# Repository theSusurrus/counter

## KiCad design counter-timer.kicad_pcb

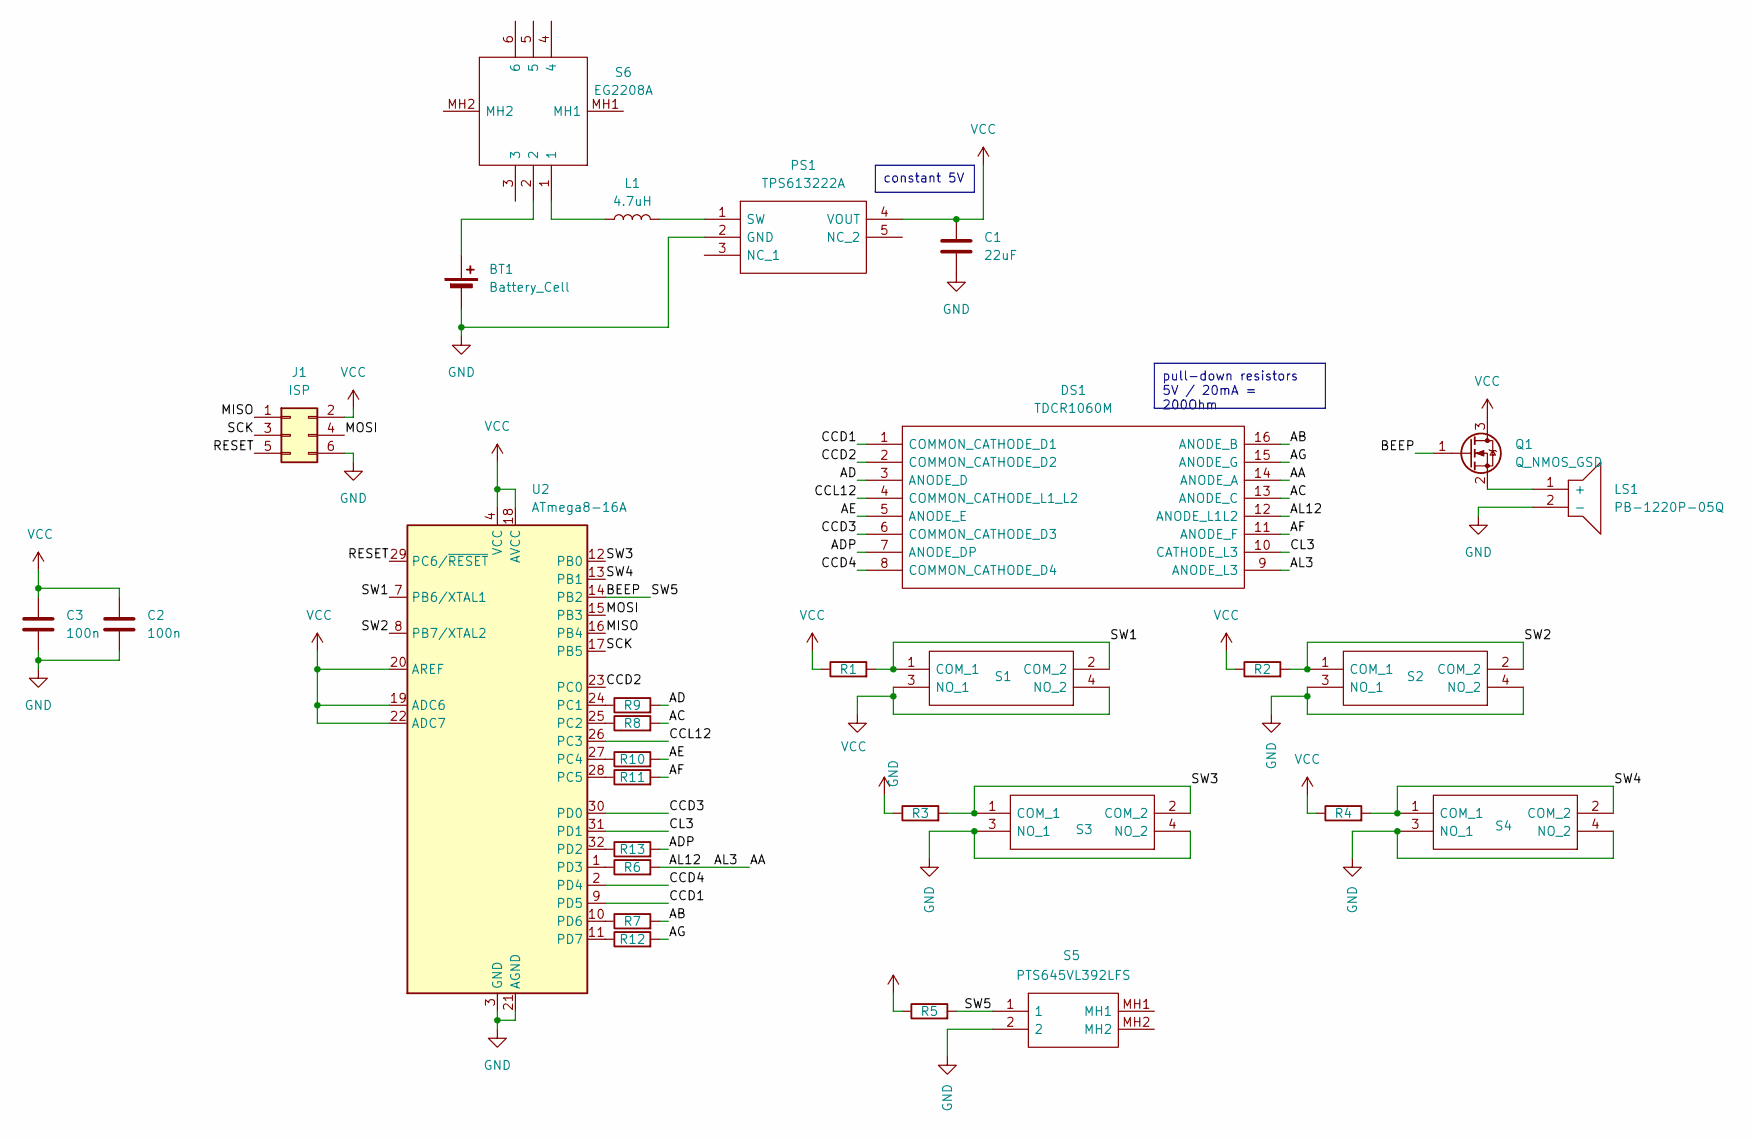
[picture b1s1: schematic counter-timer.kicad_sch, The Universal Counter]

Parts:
BT1: Battery_Cell; 12BH311PRGR
C1: 22uF; C_0603_1608Metric_Pad1.08x0.95mm_HandSolder
C2, C3: 100n; C_0603_1608Metric_Pad1.08x0.95mm_HandSolder
DS1: TDCR1060M; DIPS1016W50P254L4020H725Q16N; Mouser Part Number 78-TDCR1060M
J1: ISP; PinHeader_2x03_P2.54mm_Vertical
L1: 4.7uH; L_2512_6332Metric_Pad1.52x3.35mm_HandSolder
LS1: PB-1220P-05Q; PB1220P05Q; Mouser Part Number 539-PB-1220P-05Q
PS1: TPS613222A; SOT95P280X145-5N; Mouser Part Number 595-TPS613221ADBVR
Q1: Q_NMOS_GSD; TSOT-23_HandSoldering
R1, R2, R3, R4, R5: 1k; R_0603_1608Metric_Pad0.98x0.95mm_HandSolder
R6, R7, R8, R9, R10, R11, R12, R13: 200; R_0603_1608Metric_Pad0.98x0.95mm_HandSolder
S1, S2, S3, S4: FSM6JH; Mouser Part Number 506-FSM6JH
S5: PTS645VL392LFS; Mouser Part Number 611-PTS645VL392
S6: EG2208A; Mouser Part Number 612-EG2208A
U2: ATmega8-16A; TQFP-32_7x7mm_P0.8mm

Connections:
/AA: DS1.9 (ANODE_L3), DS1.12 (ANODE_L1L2), DS1.14 (ANODE_A), R6.2
/AB: DS1.16 (ANODE_B), R7.2
/AC: DS1.13 (ANODE_C), R8.2
/AD: DS1.3 (ANODE_D), R9.2
/ADP: DS1.7 (ANODE_DP), R13.2
/AE: DS1.5 (ANODE_E), R10.2
/AF: DS1.11 (ANODE_F), R11.2
/AG: DS1.15 (ANODE_G), R12.2
/BEEP: Q1.1 (G), R5.2, S5.1, U2.14 (PB2)
/CCD1: DS1.1 (COMMON_CATHODE_D1), U2.9 (PD5)
/CCD2: DS1.2 (COMMON_CATHODE_D2), U2.23 (PC0)
/CCD3: DS1.6 (COMMON_CATHODE_D3), U2.30 (PD0)
/CCD4: DS1.8 (COMMON_CATHODE_D4), U2.2 (PD4)
/CCL12: DS1.4 (COMMON_CATHODE_L1_L2), U2.26 (PC3)
/CL3: DS1.10 (CATHODE_L3), U2.31 (PD1)
/MISO: J1.1, U2.16 (PB4)
/MOSI: J1.4, U2.15 (PB3)
/RESET: J1.5, U2.29 (PC6/~RESET)
/SCK: J1.3, U2.17 (PB5)
/SW1: R1.2, S1.1 (COM_1), S1.2 (COM_2), U2.7 (PB6/XTAL1)
/SW2: R2.2, S2.1 (COM_1), S2.2 (COM_2), U2.8 (PB7/XTAL2)
/SW3: R3.2, S3.1 (COM_1), S3.2 (COM_2), U2.12 (PB0)
/SW4: R4.2, S4.1 (COM_1), S4.2 (COM_2), U2.13 (PB1)
GND: BT1.2 (-), C1.2, C2.2, C3.2, J1.6, LS1.2 (-), PS1.2 (GND), S1.3 (NO_1), S1.4 (NO_2), S2.3 (NO_1), S2.4 (NO_2), S3.3 (NO_1), S3.4 (NO_2), S4.3 (NO_1), S4.4 (NO_2), S5.2, U2.3 (GND), U2.5 (GND), U2.21 (AGND)
unnamed: BT1.1 (+), S6.2
unnamed: L1.1, S6.1
unnamed: LS1.1 (+), Q1.2 (S)
unnamed: L1.2, PS1.1 (SW)
unnamed: R9.1, U2.24 (PC1)
unnamed: R8.1, U2.25 (PC2)
unnamed: R10.1, U2.27 (PC4)
unnamed: R11.1, U2.28 (PC5)
unnamed: R13.1, U2.32 (PD2)
unnamed: R6.1, U2.1 (PD3)
unnamed: R7.1, U2.10 (PD6)
unnamed: R12.1, U2.11 (PD7)
VCC: C1.1, C2.1, C3.1, J1.2, PS1.4 (VOUT), Q1.3 (D), R1.1, R2.1, R3.1, R4.1, R5.1, U2.4 (VCC), U2.6 (VCC), U2.18 (AVCC), U2.19 (ADC6), U2.20 (AREF), U2.22 (ADC7)

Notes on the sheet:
constant 5V
pull-down resistors 5V / 20mA = 200Ohm

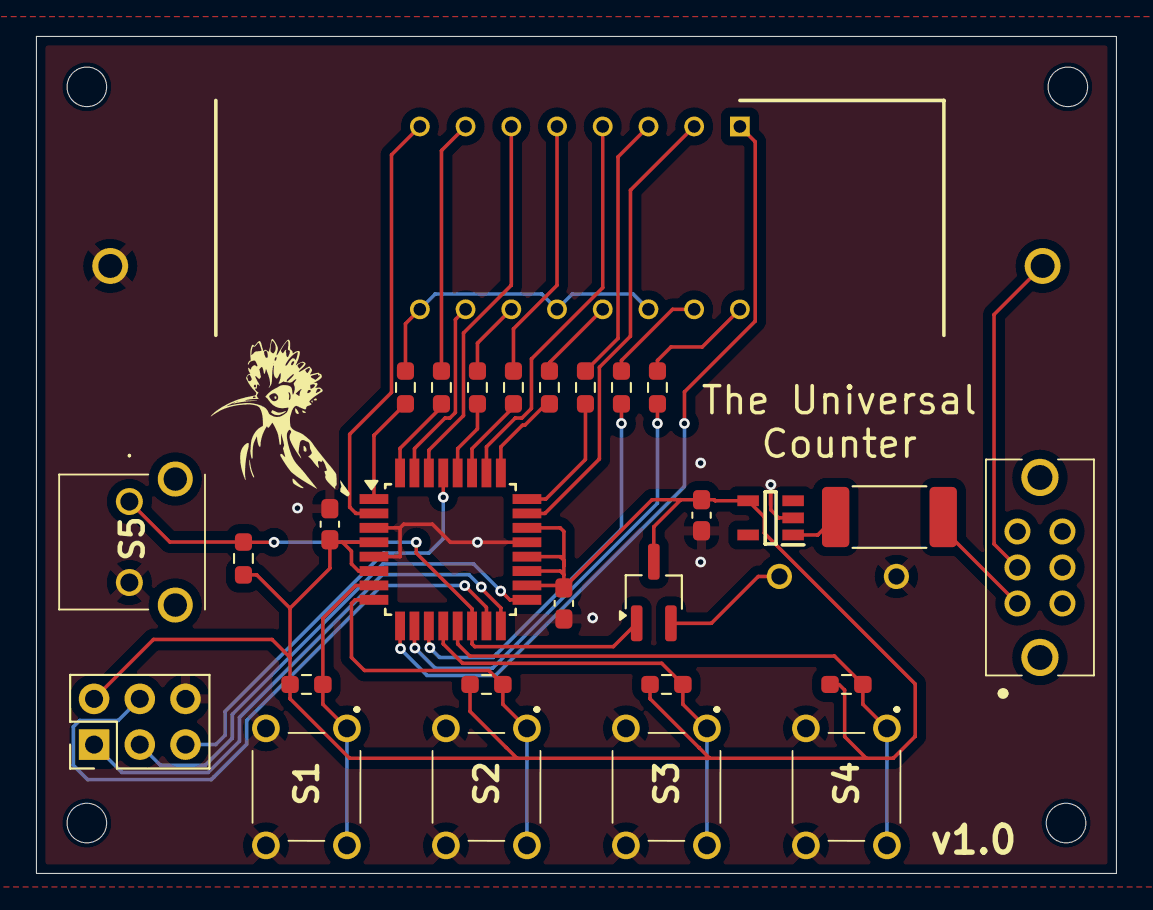
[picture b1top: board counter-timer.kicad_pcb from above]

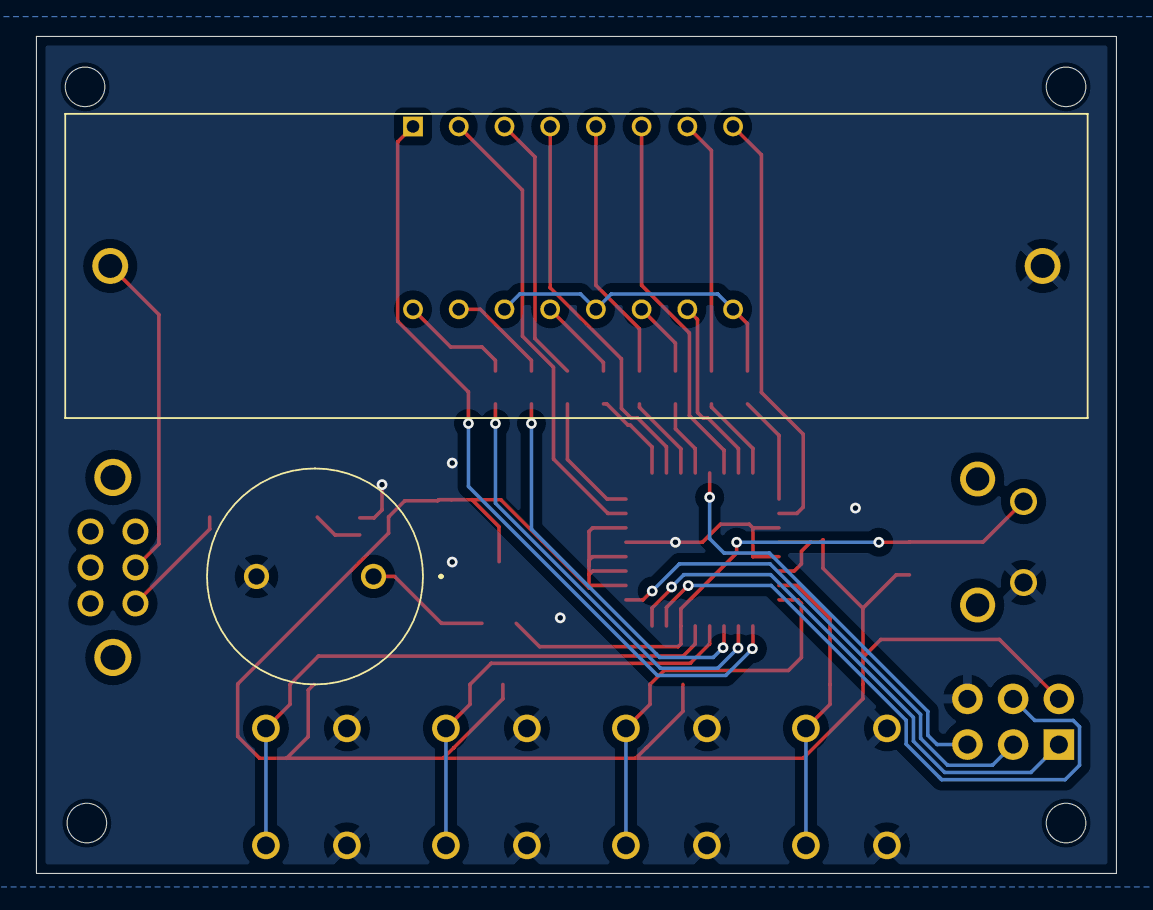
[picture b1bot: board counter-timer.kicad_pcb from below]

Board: 2 copper layers, 60.0 x 46.5 mm, 30 parts (2 on the bottom side), 37 nets.

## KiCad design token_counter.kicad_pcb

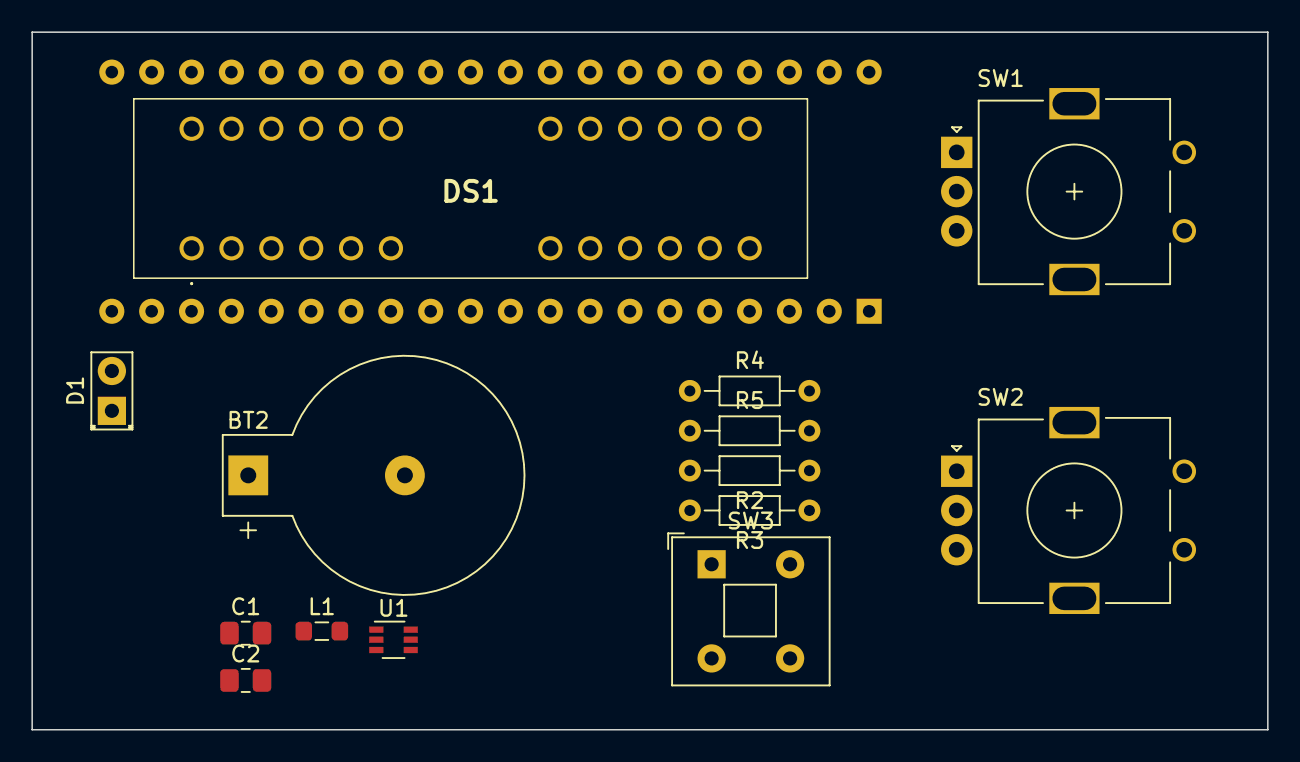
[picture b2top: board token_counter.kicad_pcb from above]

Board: 2 copper layers, 78.7 x 44.4 mm, 15 parts (1 on the bottom side), 21 nets, no tracks yet.

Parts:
BT2: Battery_Cell; BatteryHolder_Keystone_500
C1, C2: 10u; C_0805_2012Metric_Pad1.18x1.45mm_HandSolder
D1: LED; LED_D2.0mm_W4.8mm_H2.5mm_FlatTop
DS1: HDSP-2533; HDSP2533
L1: 4.7u; L_0805_2012Metric_Pad1.05x1.20mm_HandSolder
R2, R3, R4, R5: R; R_Axial_DIN0204_L3.6mm_D1.6mm_P7.62mm_Horizontal
SW1, SW2: RotaryEncoder_Switch; RotaryEncoder_Alps_EC11E_Vertical_H20mm
SW3: SW_DIP_x01; SW_Push_2P1T_Toggle_CK_PVA1xxH1xxxxxxV2
U1: TPS61222DCK; Texas_R-PDSO-G6
U2: ATmega16-16P; DIP-40_W15.24mm

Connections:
GND: BT2.2 (-), C1.2, C2.2, DS1.16 (GND_(SUPPLY)), DS1.18 (GND_(LOGIC)), R4.2, SW3.1, U1.3 (GND), U2.11 (GND), U2.31 (GND)
unnamed: BT2.1 (+), C1.1, L1.1, U1.1 (VIN)
unnamed: D1.2 (A), U2.40 (PA0)
unnamed: D1.1 (K), R4.1
unnamed: L1.2, U1.5 (L)
VCC: C2.1, DS1.11 (CLS), DS1.15 (VDD), R2.2, R3.2, R5.2, SW1.C, SW2.C, U1.2 (FB), U1.4 (VOUT), U2.10 (VCC), U2.30 (AVCC)
mcu reset: R3.1, SW3.2, U2.9 (~RESET)
pb0: R5.1, U2.1 (PB0)
pb1: SW1.A, U2.2 (PB1), U2.39 (PA1)
pb2: SW1.B, U2.3 (PB2), U2.38 (PA2)
pb3: R2.1, U2.4 (PB3)
pb4: SW2.A, U2.5 (PB4)
pb5: SW2.B, U2.6 (PB5)
pc0: DS1.29 (D6), U2.22 (PC0)
pc1: DS1.28 (D5), U2.23 (PC1)
pc2: DS1.27 (D4), U2.24 (PC2)
pc3: DS1.26 (D3), U2.25 (PC3)
pc4: DS1.25 (D2), U2.26 (PC4)
pc5: DS1.21 (D1), U2.27 (PC5)
pc6: DS1.20 (D0), U2.28 (PC6)
pd7: DS1.30 (D7), U2.21 (PD7)

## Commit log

2024-03-25 Add .gitignore for KiCAD
2024-03-25 Add HDSP-2533 based draft
2024-09-30 Add v1.0 based on TDCR1060M
2024-11-18 Add gerber output
